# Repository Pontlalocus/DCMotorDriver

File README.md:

# Project:  BJT HS DC Motor Driver

## DCMotorDriver
DC Motor Driver Simple Board using Bipolar Junction Transistor (BJT).

# 1.0  Glosary

**BJT** - Bipolar Junction Transistor

**DC** - Direct Current

**Qty**  - Quantity

**Mon** - Monitor

**PCB** - Printed Circuit Board

**Ref Des** - Reference Designator

## 2.0  Overview

DC Motor Driver board is a shield for Arduino nano to drive motors on the simplest way possible.   It uses only high side driver suply to the motor with Bipolar Junction Transistors (BJT).

The Board can handle 4 Motors each of the motors are connected to the V(+) and V(-) directly to the output.  No other connections to drive th motors are required.

This board will only operate as a high side driver with 4 oputputs that can handle PWM pulses.  The PWM pulses are internally generated on the Arduino nano.   It is important that the Arduino nano is assembled to the board and programmed with the correct software for the motors to be able to work.

The board is capable of reading the current of each motor independently by using a shunt resistor to ground.   The current measurement is injected to the Analaog port of the Arduino Nano.   We use the Ports A0 to A3 to each of the motor current.  More information on how to read the values is explained below.

## 3.0  Block Diagram

## 4.0  External Connections   

## 4.1  Main Connector Pinout

|  Ref Des      | Pin #         | Signal Name   | Description        |
| ------------- |---------------| --------------|--------------------|
| P7            | 1             | Vin           |  Power Battery     |
| P7            | 2             | GND           |  Ground            |
| P7            | 3             | 1-TX          |  Serial TX         |
| P7            | 4             | 0-RX          |  Serial RX         |
| P7            | 5             | GND           |  Ground            |
| P7            | 6             | Motor1-V+     |  Motor1(+)         |
| P7            | 7             | Motor1-V-     |  Motor1(-)         |
| P7            | 8             | Motor2-V+     |  Motor2(+)         |
| P7            | 9             | Motor2-V-     |  Motor2(-)         |
| P7            | 10            | Motor3-V+     |  Motor3(+)         |
| P7            | 11            | Motor3-V-     |  Motor3(-)         |
| P7            | 12            | Motor4-V+     |  Motor4(+)         |
| P7            | 13            | Motor4-V-     |  Motor4(-)         |
| P7            | 14            | GND           |  Ground            |
| P7            | 15            | +5V           |  Power +5V         |

## 4.2  Arduino Nano Connector

|  Ref Des      | Pin #         | Signal Name      | Description         |
| ------------- |---------------| -----------------|---------------------|
| P1            | 1             | 1-TX             |  Serial TX          |
| P1            | 2             | 0-RX             |  Serial RX          |
| P1            | 3             | Reset            |  Reset              |
| P1            | 4             | GND              |  Ground             |
| P1            | 5             | 2-PWM1           |  Motor1 - PWM1      |
| P1            | 6             | 3-PWM2           |  Motor2 - PWM2      |
| P1            | 7             | 4-PWM3           |  Motor3 - PWM3      |
| P1            | 8             | 5-PWM4           |  Motor4 - PWM4      |
| P1            | 9             | 6-ESC1           |  Reserved           |
| P1            | 10            | Not Used         |  Not Used           |
| P1            | 11            | Not Used         |  Not Used           |
| P1            | 12            | Not Used         |  Not Used           |
| P1            | 13            | Not Used         |  Not Used           |
| P1            | 14            | Not Used         |  Not Used           |
| P1            | 15            | Not Used         |  Not Used           |
| P2            | 1             | Vin              |  Power Battery      |
| P2            | 2             | GND              |  Ground             |
| P2            | 3             | Reset            |  Reset              |
| P2            | 4             | +5V              |  Power +5V          |
| P2            | 5             | Not Used         |  Not Used           |
| P2            | 6             | Not Used         |  Not Used           |
| P2            | 7             | Not Used         |  Not Used           |
| P2            | 8             | A4 - Battery_V   |  Battery Voltage IN |
| P2            | 9             | A3 - Motor4_iout | Motor 4 current Mon |
| P2            | 10            | A2 - Motor3_iout | Motor 3 current Mon |
| P2            | 11            | A1 - Motor2_iout | Motor 2 current Mon |
| P2            | 12            | A0 -  Motor2_iout| Motor 1 current Mon |
| P2            | 13            | AREF             | Not Used            |
| P2            | 14            | +3.3V            | Power 3.3V          |
| P2            | 15            | 13 - SCK         | Serial Clock        |

## 5.0  General Specifications

General Specifications include typical operation specifications

## 5.1  Typical Specifications

**Operation Voltage**: Battery Vin must be equal to 9V +/- 1V
**Operating Temperature**: 0°C to 40°C
**Battery Input Current**:
1.  No Load = <_Pending_>.
2.  Individual Motor Max Load =<_xx A_>.
3.  All Motors Max Load = <_xx A_>.

**Battery Voltage Monitor Range**:  VBAT * 0.5.

**Battery Monitor Low Pass Filter**: <_Pending_>.

**Motor Current Monitor Formula**: Current * 0.1 in Amps.

**Motor Current Low Pass Filter**: <_Pending_>.

_Note: Motor current is same formula for all motors: Motor1, Motor2, Motor3 and Motor4

##  Project Design

## 6.1  Schematic Diagram

Refer to Schematic Diagram for wiring connections of the Project

This project requires the Arduino Nano board to be used.  For information on the schematic diagram of the Arduino Nano please refer to the following page

Note: External Link

## 6.2 Bill of Material

The following list of components are selected for the Design.  All are discrete components:

|  Item #       | Description                      | Qty | Reference Designator                                           |
| ------------- |----------------------------------| ----|----------------------------------------------------------------|
| 1             | PCB bare boards FR-4 Tg=140 2L   | 1   |  PCB 1                                                         |
| 2             | DIODE GEN PURP 250V 200MA SOD323 | 8   |  D2 D3 D7 D5 D8 D6 D9 D10                                      |
| 3             | CAP CER 10000PF 50V X7R 0603     | 5   |  C3 C9 C11 C19 C26                                             |
| 4             | CAP CER 0.1UF 50V X7R 0603       | 17  |  C6 C8 C17 C18 C23 C1 C2 C5 C15 C16 C22 C24 C25                |
| 5             | CAP CER 10UF 16V X7R 0805        | 4   |  C7 C13 C14 C21                                                |
| 6             | TRANS PNP 80V 4A SOT89           | 4   |  Q2 Q5 Q6 Q8                                                   |
| 7             | TRANS PREBIAS NPN 246MW SOT23-3  | 4   |  Q1 Q3 Q4 Q7                                                   |
| 8             | RES 0.01 OHM 1% 1/4W 0603        | 4   |  R5 R10 R11 R16                                                |
| 9             | RES SMD 10K OHM 5% 1/10W 0603    | 4   |  R2 R8 R9 R15                                                  |
| 10            | RES SMD 47K OHM 5% 1/10W 0603    | 6   |  R4 R12 R13 R17 R18 R19                                        |
| 11            | RES SMD 0 OHM JUMPER 1/10W 0603  | 0   |                                                                |
| 12            | RES SMD 680 OHM 1% 1/8W 0805     | 4   |  R3 R6 R7 R14                                                  |
| 13            | DIODE GEN PURP 400V 5A DO214AB   | 1   |  D1                                                            |
| 14            | TVS DIODE 10V 17V DO214AA        | 1   |  D4                                                            |
| 15            | Arduino Nano Board               | 1   |  BOARD 1                                                       |

The following list are components that are not assembled in the board

### Not Assembled 
C4 C10 C12 C20 R1

## 6.3  PCB Specification

PCB Board is FR-4.  Tickness 1.6mm.  2 layers.  Top Side Assembly.  Silkscreen in Top Side only.

Supplier selected for the first Job is JLPCB

### 6.3.1 PCB Design Top View 

### 6.3.2 PCB Design Bottom View

##  7.0  Design Verification

For making sure the board functioanlity is working correctly the following Components are used.  Follow the connection diagram and test the functioanlity of the board with this Software

## 7.1  External Components Requirements

Required External Components

### 7.1.1  Power Pack

Power Pack: 9V
Example:
<_Pending_>.

### 7.1.2  DC Voltage Regulator

DC Voltage Regulator 5V
Example:
<_Pending_>.

### 7.1.3  DC Motor

2.  DC Motor: 
Example:
<_Pending_>.

## 7.2  Design Verification Connections

Todo:  Add connections to system with actual pictures

## 7.3  Design Verification Software

Todo:  Software components,  How does the software works, how to flash software,  how to run software, 

## 7.4  Measure of the output signals and confirmation of General Specifications

Todo:  use a measurement device to confirm General Specifications:  Supply Voltage, Actual current vs adruino measured x 4, PWM signal x 4, Battery Monitor. 

## 8.0  Future Generation Improvements

### 8.1 TODO
1.  Add MQTT RF Transmitter
2.  Add Sensors for 3 axis accelerometer, Gyroscpe and Compass
3.  Add Output for Servo

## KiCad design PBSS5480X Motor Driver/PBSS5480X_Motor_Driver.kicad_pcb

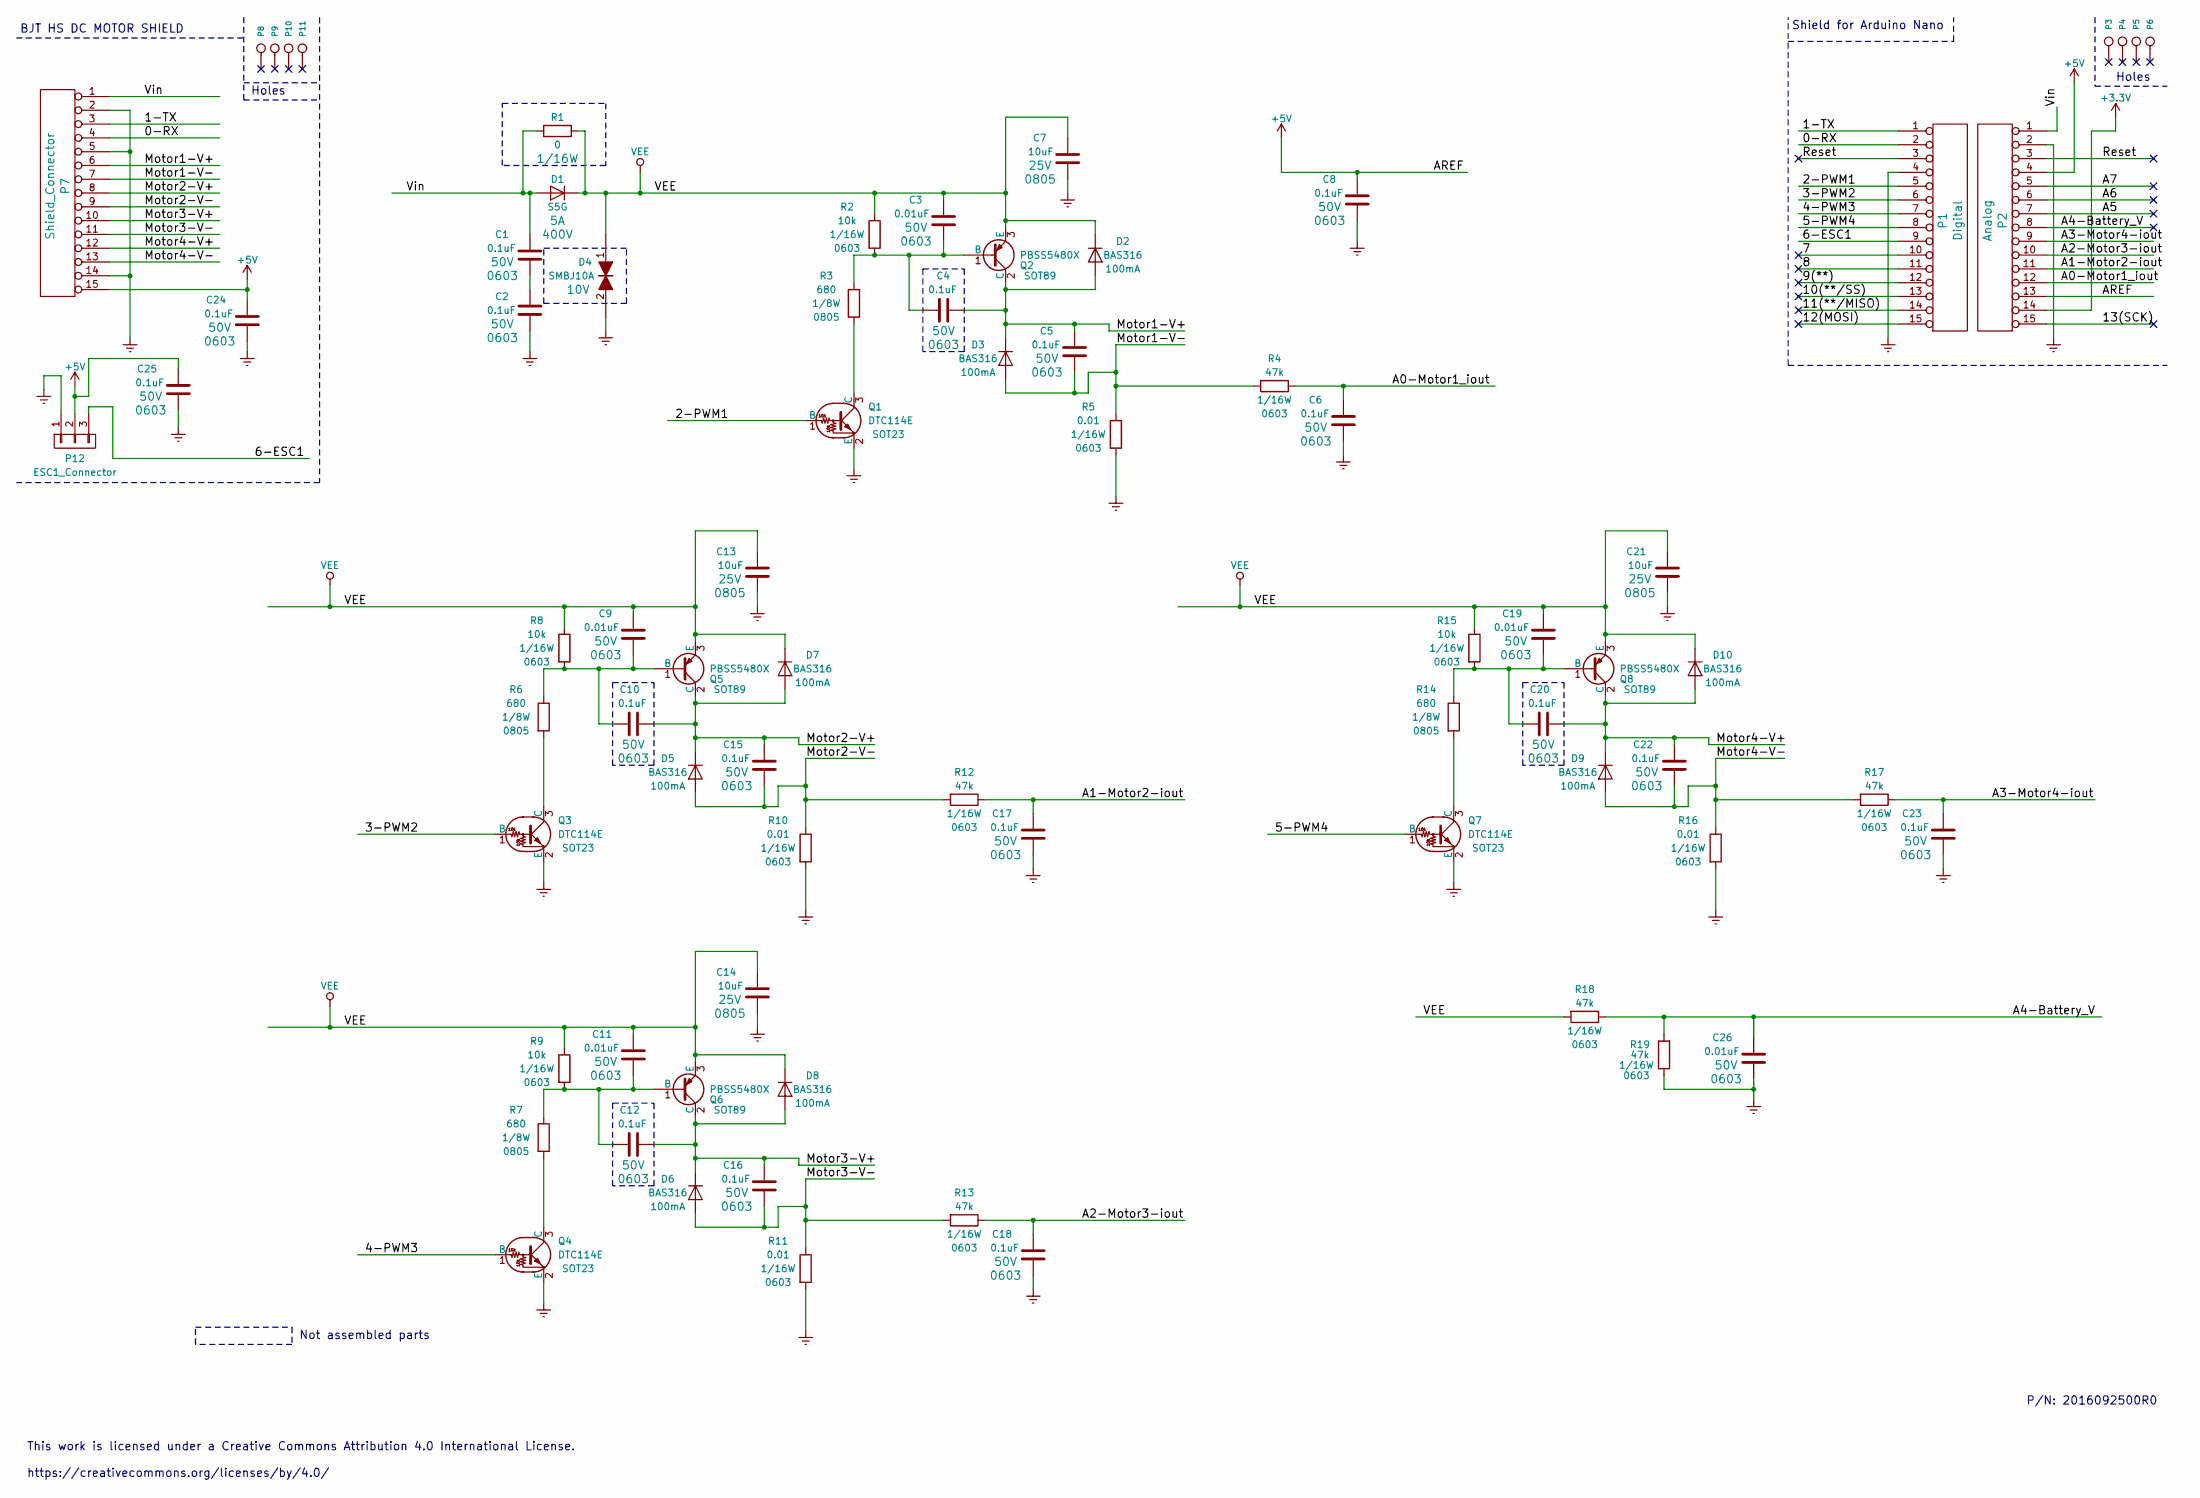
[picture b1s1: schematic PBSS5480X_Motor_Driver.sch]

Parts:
C1, C2, C4, C5, C6, C8, C10, C12, C15, C16, C17, C18, C20, C22, C23, C24, C25: 0.1uF; C_0603; Rating 50V; MfrPN GRM188R71H104KA93D
C3, C9, C11, C19, C26: 0.01uF; C_0603; Rating 50V; MfrPN GRM188R71H103KA01D
C7, C13, C14, C21: 10uF; C_0805; Rating 25V; MfrPN GRM21BR71A106KA73L
D1: S5G; SMC_Standard; MfrPN S5G-E3/57T
D2, D3, D5, D6, D7, D8, D9, D10: BAS316; SOD-323; MfrPN BAS316,115
D4: SMBJ10A; SMB_Standard; Voltage 10V; MfrPN SMBJ10A-E3/52
P1: Digital; Socket_Strip_Arduino_1x15
P2: Analog; Socket_Strip_Arduino_1x15
P3, P4, P5, P6: CONN_1; 1pin_Nano
P7: Shield_Connector; Socket_Strip_Arduino_1x15
P8, P9, P11: CONN_1; 1pin-5.1mmx7mm
P10: CONN_1; 1pin-5.1mm
P12: ESC1_Connector; PINHEAD1-3
Q1, Q3, Q4, Q7: DTC114E; SOT-23; MfrPN PDTC114ET,215
Q2, Q5, Q6, Q8: PBSS5480X; SOT89-3_Housing; MfrPN PBSS5480X,135
R1: 0; R_0603; Rating 1/16W; MfrPN RC0603JR-070RL
R2, R8, R9, R15: 10k; R_0603; Rating 1/16W; MfrPN RC0603FR-0710KL
R3, R6, R7, R14: 680; R_0805; Rating 1/8W; MfrPN RC0805FR-07680RL
R4, R12, R13, R17, R18, R19: 47k; R_0603; Rating 1/16W; MfrPN RC0603FR-0747KL
R5, R10, R11, R16: 0.01; R_0603; Rating 1/16W; MfrPN PE0603DRF070R01L

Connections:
+3V3: P2.14
+5V: C8.2, C24.2, C25.2, P2.4, P2.13, P7.15 (p15), P12.2
/0-RX: P1.2, P7.4
/1-TX: P1.1, P7.3
/2-PWM1: P1.5, Q1.1 (B)
/3-PWM2: P1.6, Q3.1 (B)
/4-PWM3: P1.7, Q4.1 (B)
/5-PWM4: P1.8, Q7.1 (B)
/6-ESC1: P1.9, P12.3
/7: P1.10
/8: P1.11
/9(**): P1.12
/10(**/SS): P1.13
/11(**/MISO): P1.14
/12(MOSI): P1.15 (p15)
/13(SCK): P2.15 (p15)
/A0-Motor1_iout: C6.2, P2.12, R4.1
/A1-Motor2-iout: C17.2, P2.11, R12.1
/A2-Motor3-iout: C18.2, P2.10, R13.1
/A3-Motor4-iout: C23.2, P2.9, R17.1
/A4-Battery_V: C26.2, P2.8, R18.1, R19.2
/A5: P2.7
/A6: P2.6
/A7: P2.5
/Motor1-V+: C4.2, C5.2, D2.2 (A), D3.1 (K), P7.6, Q2.2 (C)
/Motor1-V-: C5.1, D3.2 (A), P7.7, R4.2, R5.1
/Motor2-V+: C10.2, C15.2, D5.1 (K), D7.2 (A), P7.8, Q5.2 (C)
/Motor2-V-: C15.1, D5.2 (A), P7.9, R10.1, R12.2
/Motor3-V+: C12.2, C16.2, D6.1 (K), D8.2 (A), P7.10, Q6.2 (C)
/Motor3-V-: C16.1, D6.2 (A), P7.11, R11.1, R13.2
/Motor4-V+: C20.2, C22.2, D9.1 (K), D10.2 (A), P7.12, Q8.2 (C)
/Motor4-V-: C22.1, D9.2 (A), P7.13, R16.1, R17.2
/Reset: P1.3, P2.3
/Vin: C1.2, D1.2 (A), P2.1, P7.1, R1.2
GNDREF: C2.1, C6.1, C7.1, C8.1, C13.1, C14.1, C17.1, C18.1, C21.1, C23.1, C24.1, C25.1, C26.1, D4.2, P1.4, P2.2, P7.2, P7.5, P7.14, P12.1, Q1.2 (E), Q3.2 (E), Q4.2 (E), Q7.2 (E), R5.2, R10.2, R11.2, R16.2, R19.1
unnamed: C1.1, C2.2
unnamed: C3.1, C4.1, Q2.1 (B), R2.2, R3.1
unnamed: C9.1, C10.1, Q5.1 (B), R6.1, R8.2
unnamed: C11.1, C12.1, Q6.1 (B), R7.1, R9.2
unnamed: C19.1, C20.1, Q8.1 (B), R14.1, R15.2
unnamed: Q1.3 (C), R3.2
unnamed: Q3.3 (C), R6.2
unnamed: Q4.3 (C), R7.2
unnamed: Q7.3 (C), R14.2
VEE: C3.2, C7.2, C9.2, C11.2, C13.2, C14.2, C19.2, C21.2, D1.1 (K), D2.1 (K), D4.1, D7.1 (K), D8.1 (K), D10.1 (K), Q2.3 (E), Q5.3 (E), Q6.3 (E), Q8.3 (E), R1.1, R2.1, R8.1, R9.1, R15.1, R18.2

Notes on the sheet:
Holes
Shield for Arduino Nano
BJT HS DC MOTOR SHIELD
Not assembled parts
This work is licensed under a Creative Commons Attribution 4.0 International License. https://creativecommons.org/licenses/by/4.0/
P/N: 2016092500R0

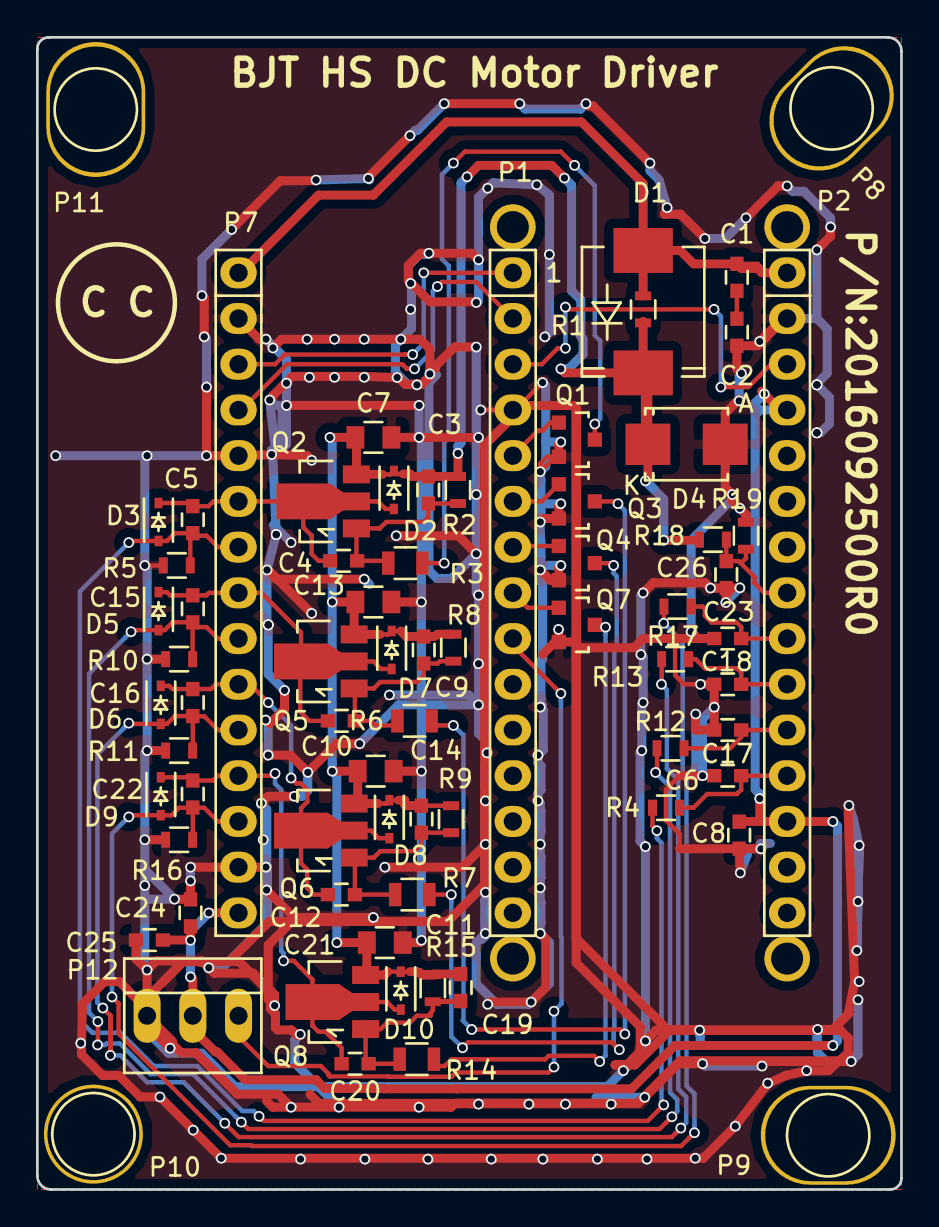
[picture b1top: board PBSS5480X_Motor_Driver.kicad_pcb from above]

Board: 2 copper layers, 48.0 x 64.0 mm, 75 parts (0 on the bottom side), 34 nets.

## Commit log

2018-03-17 :boom::camel: Added .gitattributes & .gitignore files
2018-03-17 Initil Repository for PBSS5480x
2019-01-16 Release 0.01
    First Release for Board Creation
2019-01-16 Rev 0.02 Kicad 5.02 Conversion
    Convert Kicad 5.02 and Uploaded Schematic Diagram
2019-01-27 Creating Documentation
    Continue Documentation adding board assembly information
2019-01-27 Updated Readme.md
    Added documentation
2019-01-27 Update README.md
    Added Indexes to Documentation to easy follow the document
2019-01-27 Block Diagram and License
    Added License information and Block Diagram
2019-01-27 Image
    Testing Link
2019-01-27 Documentation update
    Added documentation Block Diagram png and Schematic diagram in png on docs
2019-01-27 Update README.md
    Added link to Schematic diagram png file
2019-01-27 Update README.md
    Added BOM
2019-01-27 Updates
    updated block diagram to show the battery monitor and power feed for motor drivers
2019-02-17 Added Not Assembled Components
    The list of not assembled components was added by the results of the first assembled board
